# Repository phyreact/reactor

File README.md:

# Reactor

**A world that can be seen, heard, and sensed.**

Someone calls from across the room. A hand moves beside the camera. The surface
under a device shifts. Each moment carries a cue about what is happening nearby.

We want to build machines that can notice those cues and respond in ways people
understand. Reactor explores that idea through two devices: an expressive robot
and a compact sensing hub. They share a Radxa ZERO 3W host and four-microphone
audio, with different bodies and ways to interact.

## Meet the projects

| Donald Microduck | Mickey Hub |
| :--- | :--- |
|  |  |
| **Give listening a body.** A small robot with four microphones, a camera, a speaker and 15 smart servos. | **Bring perception together.** Four microphones, three radars, a camera, depth sensing, motion sensors and dual displays. |
| [**Explore Donald Microduck →**](donald-microduck/) | [**Explore Mickey Hub →**](mickeyhub/) |

Each project has its own guide, animated previews, STL parts, one final assembled
Blender model, firmware and build instructions. The GIFs above show the devices rotating, separating
into modules and coming back together, with English explanations.

## What you can explore

| Area | Donald Microduck | Mickey Hub |
| --- | --- | --- |
| Hearing | Four-microphone ReSpeaker hardware; current firmware provides 16 kHz stereo processed audio. | Four-microphone ReSpeaker hardware and a speaker for audio experiments. |
| Perception | Camera and motion sensing in a moving robot. | Ultra-wide camera, 8 × 8 ToF depth sensing, three radar modules, six-axis IMU and compass. |
| Interaction | Speaker, expressive pose and 15 smart servos. | Glasses-like dual displays, speaker, light ring, controls and additional I/O. |
| Design files | One final assembled Blender model and 37 printable STL parts. | One final assembled Blender model, 15 printable STL parts, four fit samples and native KiCad projects. |
| Development | [Firmware](donald-microduck/firmware/) · [Host tools](donald-microduck/software/) · [Simulation](donald-microduck/sim/) | [Firmware](mickeyhub/firmware/) · [Electronics](mickeyhub/electronics/) · [Simulation](mickeyhub/simulation/) |

These are evolving hardware projects. Sound-source localization, sensor fusion
and autonomous responses are development goals. Each project guide distinguishes
the supplied files and recorded checks from work that still needs assembled
hardware testing.

## Start exploring

1. **Choose a project above.** Its README introduces the device and points to the relevant files.
2. **Retrieve the large models with Git LFS.** Run these commands inside your checkout:

   ```sh
   git lfs install --local
   git lfs pull
   ```

3. **Open an editable assembly.** Start with
   [Donald Microduck](donald-microduck/mechanical/duck.blend) or
   [Mickey Hub](mickeyhub/mickeyhub.blend), then follow the project's build guide.

The repository includes firmware and application sources, native electronics,
manufacturing files, STL exports, one final assembled Blender file per project,
GIF previews and captions. Component GLBs, STEP references, intermediate design
files, separate animation scenes and full MP4 renders stay in the local
`memory_backups/` directory, alongside render caches and conversation history.
They are excluded from commits and source archives.

## Contribute

Work on mechanical fit, audio processing, perception, firmware, host applications
and interaction design is welcome. Identify the affected project, explain the
change and include the checks needed to reproduce your result.

## Licenses

| Project | Terms |
| --- | --- |
| **Donald Microduck** | Preserves the official upstream Apache-2.0 software license and the upstream noncommercial, share-alike model notice. [Upstream terms](donald-microduck/UPSTREAM_LICENSES.md). |
| **Mickey Hub** | First-party designs and content: **CC BY-NC 4.0**. First-party firmware and tools: **PolyForm Noncommercial 1.0.0**. Additional permission allows **up to 100 covered units sold per entity per calendar year** without a license fee. [License](mickeyhub/LICENSE). |

Mickey Hub's [limited commercial permission](mickeyhub/COMMERCIAL_USE.md)
covers up to and including 100 devices or one-device kits sold by the same
individual or legal entity each calendar year. Before selling the 101st unit,
obtain separate written authorization from the Reactor maintainers.
The complete grant defines the counting rules and third-party exclusions.

Original shared documentation and graphics use CC BY-NC 4.0.
Third-party material retains its own terms. [LICENSING.md](LICENSING.md)
defines the project scopes, commercial authorization and model exceptions;
[THIRD_PARTY.md](THIRD_PARTY.md) records upstream sources.

---

<sub>For questions or commercial licensing, contact [phyreact@gmail.com](mailto:phyreact@gmail.com).</sub>

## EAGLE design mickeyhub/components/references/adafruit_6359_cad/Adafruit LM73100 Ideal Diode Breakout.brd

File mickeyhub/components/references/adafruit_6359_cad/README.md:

## Adafruit LM73100 Ideal Diode Breakout 23V 5A Max PCB

<a href="http://www.adafruit.com/products/6359"><br/>
Click here to purchase one from the Adafruit shop</a>

PCB files for the Adafruit LM73100 Ideal Diode Breakout 23V 5A Max. 

Format is EagleCAD schematic and board layout
* https://www.adafruit.com/product/6359

### Description

If your project is moving a lot of power around, and efficiency is key, an Adafruit LM73100 Ideal Diode breakout is a great way to keep your power budget tidy! As long as your power supply is 3~23V DC and up to 5A, use this in place of a diode to keep current flowing one direction. However, unlike a diode, you won't suffer a 1V+ forward drop which just gets lost as heat. Instead, the internal chip has two back-to-back FETs, with a typical Rdson of 30 mΩ. That means that even with 5A, you'll lose around 150mV. This makes it perfect for efficiency-sensitive setups like solar panels and LiPoly batteries. 

Unlike our [LM62200 dual ideal diode](https://www.adafruit.com/product/5830), this board acts as 'one' diode only - but it can handle much higher voltages and currents! There's also some niceties we added like solder-free operation thanks to on-board terminal blocks, and a green LED that will light when power is going in the right direction. You can also monitor the current draw by reading the analog voltage off of IMON, handy if you don't want a separate power monitoring kit.

To make it bread-board friendly, we've placed it on a small PCB with 9 x 0.1" breakout pads.We include a bit of header, some light soldering is required to attach the header for breadboarding use. Or you can use direct wiring to the terminal blocks if you want to insert it directly into a circuit without a breadboard.

### License

Adafruit invests time and resources providing this open source design, please support Adafruit and open-source hardware by purchasing products from [Adafruit](https://www.adafruit.com)!

Designed by Limor Fried/Ladyada for Adafruit Industries.

Creative Commons Attribution/Share-Alike, all text above must be included in any redistribution. 
See license.txt for additional details.

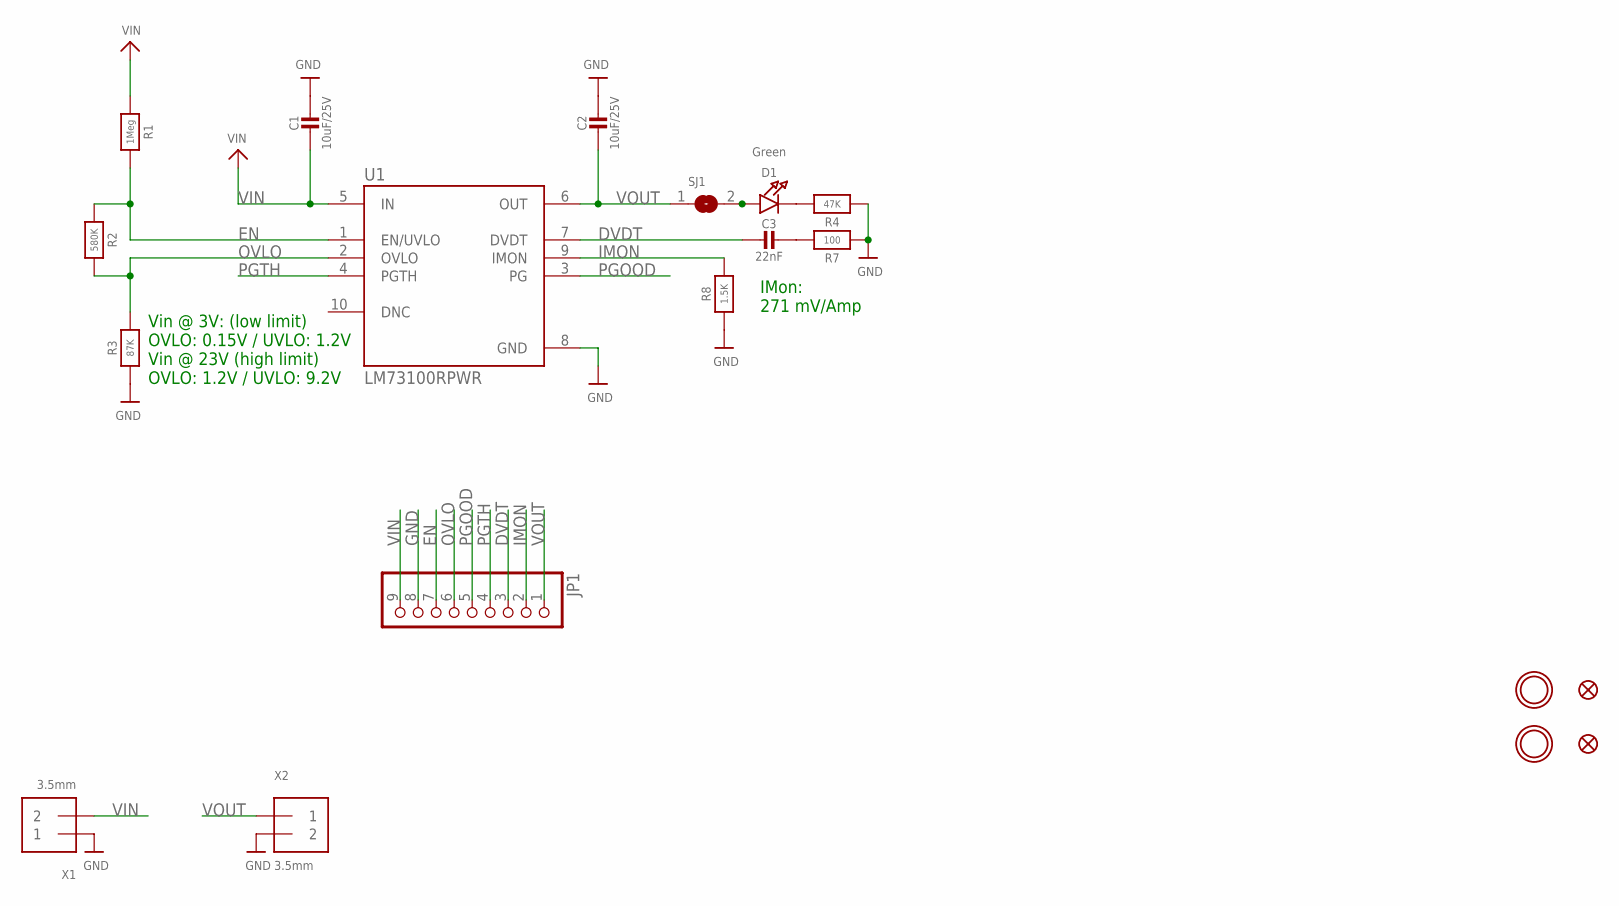
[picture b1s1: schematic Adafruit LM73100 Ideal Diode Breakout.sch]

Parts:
C1, C2: 10uF/25V; 0805-NO
C3: 22nF; 0603-NO
D1: Green; CHIPLED_0603_NOOUTLINE
FID1, FID2: FIDUCIAL_0.5MM
JP1: HEADER-1X970MIL; 1X09_ROUND_70
R1: 1Meg; 0603-NO
R2: 580K; 0603-NO
R3: 87K; 0603-NO
R4: 47K; 0603-NO
R7: 100; 0603-NO
R8: 1.5K; _0402NO
SJ1: SOLDERJUMPERCLOSED; SOLDERJUMPER_CLOSEDWIRE
U1: LM73100RPWR; IC_LM73100RPWR
U$1, U$9: MOUNTINGHOLE2.5; MOUNTINGHOLE_2.5_PLATED
X1, X2: 3.5mm; TERMBLOCK_1X2-3.5MM

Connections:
DVDT: C3.2, JP1.3, U1.7 (DVDT)
EN: JP1.7, R1.1, R2.2, U1.1 (EN/UVLO)
GND: C1.1, C2.1, JP1.8, R3.2, R4.2, R7.1, R8.1, U1.8 (GND), X1.1, X2.2
IMON: JP1.2, R8.2, U1.9 (IMON)
unnamed: C3.1, R7.2
unnamed: D1.C, R4.1
unnamed: D1.A, SJ1.2
OVLO: JP1.6, R2.1, R3.1, U1.2 (OVLO)
PGOOD: JP1.5, U1.3 (PG)
PGTH: JP1.4, U1.4 (PGTH)
VIN: C1.2, JP1.9, R1.2, U1.5 (IN), X1.2
VOUT: C2.2, JP1.1, SJ1.1, U1.6 (OUT), X2.1

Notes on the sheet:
Vin @ 3V: (low limit) OVLO: 0.15V / UVLO: 1.2V Vin @ 23V (high limit) OVLO: 1.2V / UVLO: 9.2V
IMon: 271 mV/Amp

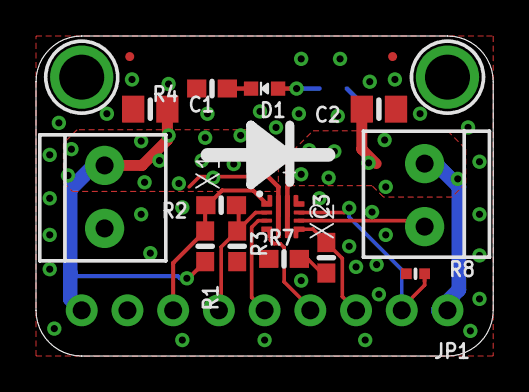
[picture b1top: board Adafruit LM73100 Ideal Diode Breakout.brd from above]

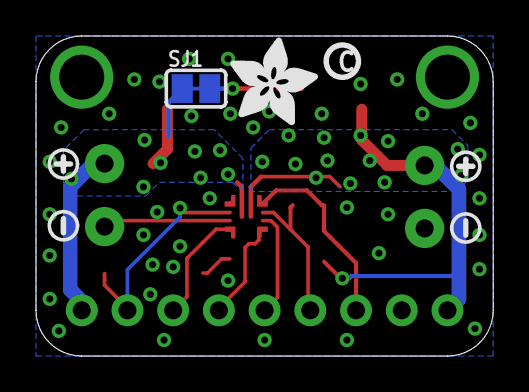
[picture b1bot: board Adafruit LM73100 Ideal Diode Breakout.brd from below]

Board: 2 copper layers, 25.4 x 17.8 mm, 45 parts (12 on the bottom side), 12 nets.

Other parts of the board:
PLABEL2: PLABEL2
PLABEL3: PLABEL3
PLABEL7: PLABEL7
PLABEL8: PLABEL8
PLABEL9: PLABEL9
PLABEL10: PLABEL10
PLABEL12: PLABEL12
PLABEL13: PLABEL13
PLABEL14: PLABEL14
PLABEL15: PLABEL15
PLABEL16: PLABEL16
PLABEL17: PLABEL17
PLABEL18: PLABEL18
PLABEL19: PLABEL19
PLABEL20: PLABEL20
PLABEL21: PLABEL21
PLABEL22: PLABEL22
PLABEL23: PLABEL23
PLABEL24: PLABEL24
PLABEL25: PLABEL25
U$10: PCBFEAT-REV-040
U$14: ADAFRUIT_5MM
U$15, U$18: SYMBOL_MINUS
U$16, U$17: SYMBOL_PLUS

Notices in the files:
parts and their libraries:
microbuilder: This work is placed in the public domain, and may be freely used for commercial and non-commercial work with the following conditions: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
